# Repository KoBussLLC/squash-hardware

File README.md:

# Squash Keyboard Hardware

Small keyboard for big brains with lots of layers
🤏 ⌨️ 🧠 🍰

This keyboard uses an acrylic case, POM switch-plate, and PCB mounted switches and stabilizers.

See Squash's bigger brother for [build instructions](https://github.com/KoBussLLC/grabert-hardware/blob/main/doc/BUILDGUIDE.md) and [additional information](https://github.com/KoBussLLC/grabert-hardware/blob/main/README.md).

## Layout

[Keyboard Layout Editor Permalink](http://www.keyboard-layout-editor.com/##@@_x:2.75&w:1.5%3B&=0,0&=0,1&=0,2&=0,3&=0,4&=0,5&=0,6&=0,7&=0,8&=0,9&=0,10&_w:1.5%3B&=0,11%3B&@_x:2.75&w:1.75%3B&=1,0&=1,1&=1,2&=1,3&=1,4&=1,5&=1,6&=1,7&=1,8&=1,9&_w:2.25%3B&=1,10%3B&@_x:0.25&w:1.25%3B&=2,0%0A%0A%0A0,1&=2,1%0A%0A%0A0,1&_x:0.25&w:2.25%3B&=2,0%0A%0A%0A0,0&=2,2&=2,3&=2,4&=2,5&=2,6&=2,7&=2,8&=2,9&=2,10&_w:1.75%3B&=2,11%3B&@_x:2.75&c=%23AAAAAA&w:1.25%3B&=3,0&=3,1&=3,2%0A%0A%0A1,0&_c=%23cccccc&w:6.25%3B&=3,4%0A%0A%0A1,0&_c=%23AAAAAA&w:1.25%3B&=3,6&=3,7&_w:1.25%3B&=3,8%3B&@_y:0.25&x:5&w:1.25%3B&=3,2%0A%0A%0A1,1&_c=%23cccccc&w:2.25%3B&=3,3%0A%0A%0A1,1&=3,4%0A%0A%0A1,1&_w:2.75%3B&=3,5%0A%0A%0A1,1&_x:4%3B&=3,11) for layout options.

A standard keycap set can be used as long as each "row" has the same profile and a 1.75u right shift key is included.

## PCB

This project uses KiCad for electrical CAD

### Electrical Design Constraings
- No diode matrix enabled by LQFP 100 Footprint
- STM32 Based Micro-controller
- USB-C
- PWM LED indicators for Caps Lock and modifiers
- PCB Mount switches
- Enocder and I2C OLED Display

## CAD

This project uses FreeCAD 0.19 for mechanical CAD. File names are prefixed with a unique, arbitrary alphanumeric code with the first character always being a alpha character.

### Required Addons
- Assembly 4
- fasteners
- kicadStepUpMod

### Mechanical Design Constraints
- 40% Keyboard Layout
- Split spacebar and left shift layout options
- Push Button Encoder
- OLED Screen
- Fully Laser Cut Case

### Acrylic Sheet Stackup

Main Case Stackup. 0 is the bottom of the case. Foot pieces are included in the D65_USBCutoutSpacer.svg file and are assembled with the smallest piece on the bottom.

| Sheet Number | FreeCAD File Name | Thickness | Material | Shape |
| - | - | - | - | - |
| 0 | O56_BottomPlate | 0.125 in | Acrylic |  |
| 1 | Y7X_ClosedSpacer | 0.125 in | Acrylic |  |
| 2 | D65_USBCutoutSpacer | 0.125 in | Acrylic |  *includes foot pieces |
| 3 | D65_USBCutoutSpacer | 0.125 in | Acrylic |  *includes foot pieces |
| 4 | S86_SwitchPlate | 0.0625 in | POM/Acetal |  |
| 5 | Y7X_ClosedSpacer | 0.125 in | Acrylic |  |
| 6 | Q45_OLEDCover | 0.125 in | Acrylic |  |
| 7 | O03_TopCover | 0.125 in | Acrylic |  |

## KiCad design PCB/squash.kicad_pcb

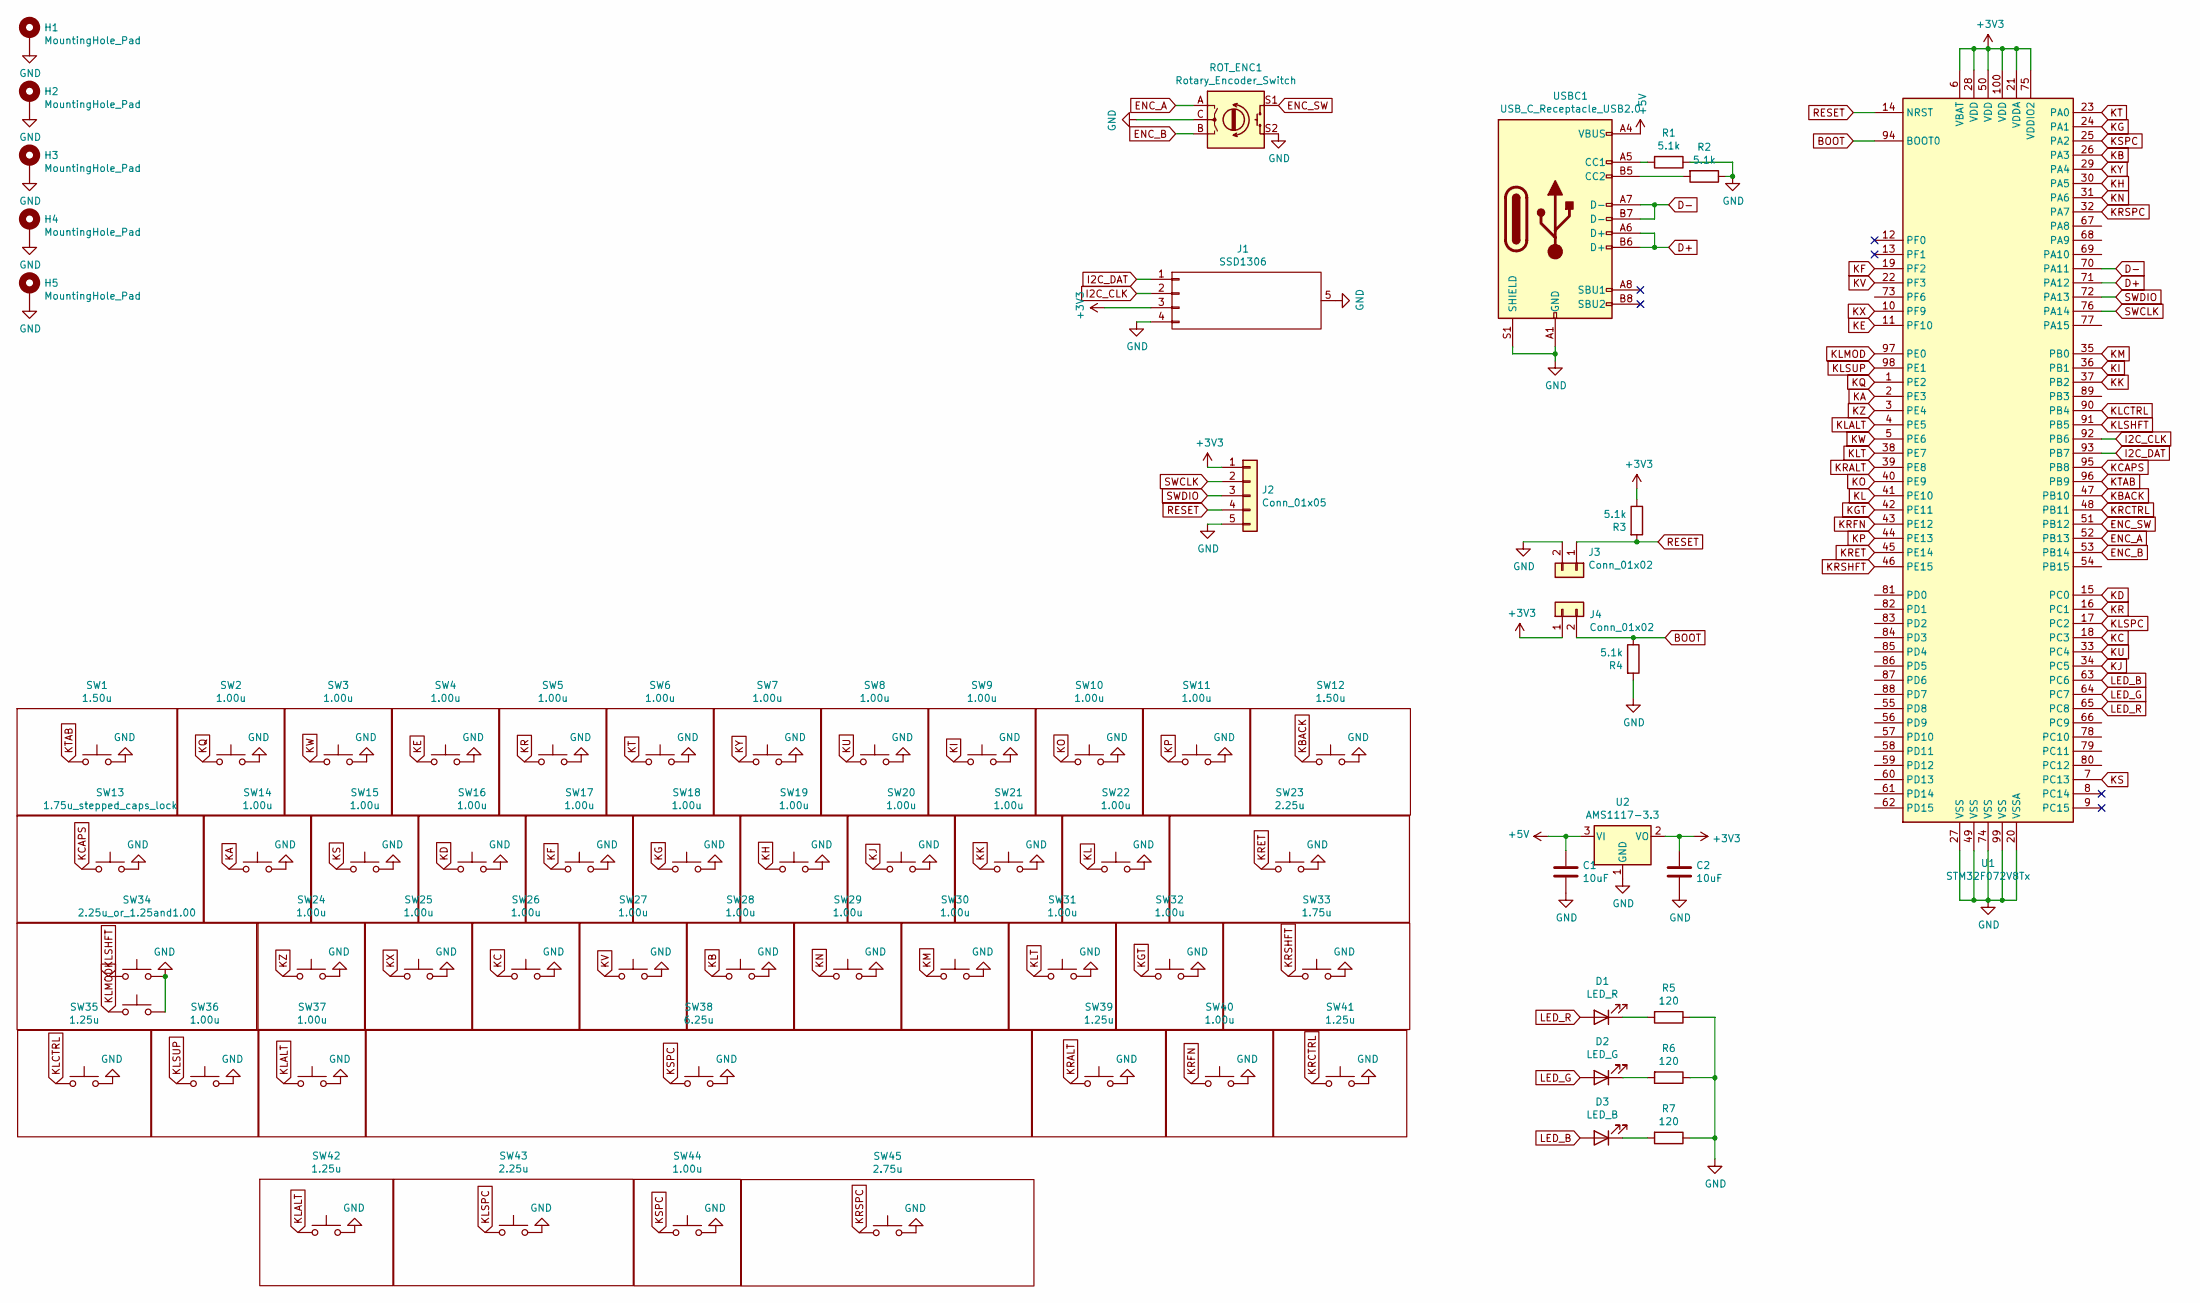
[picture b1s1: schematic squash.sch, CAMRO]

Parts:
C1, C2: 10uF; C_0603_1608Metric
D1: LED_R; LED_0603_1608Metric
D2: LED_G; LED_0603_1608Metric
D3: LED_B; LED_0603_1608Metric
H1, H2, H3, H4, H5: MountingHole_Pad; MountingHole_2.2mm_M2_Pad_Via
J1: SSD1306
J2: Conn_01x05; PinHeader_1x05_P2.54mm_Vertical
J3, J4: Conn_01x02; PinHeader_1x02_P2.54mm_Vertical
R1, R2, R3, R4: 5.1k; R_0603_1608Metric
R5, R6, R7: 120; R_0603_1608Metric
ROT_ENC1: Rotary_Encoder_Switch; RotaryEncoder_Alps_EC11E-Switch_Vertical_H20mm
SW1, SW12: 1.50u; MX_1.50u
SW2, SW3, SW4, SW5, SW6, SW7, SW8, SW9, SW10, SW11, SW14, SW15, SW16, SW17, SW18, SW19, SW20, SW21, SW22, SW24, SW25, SW26, SW27, SW28, SW29, SW30, SW31, SW32, SW36, SW37, SW40, SW44: 1.00u; MX_1u
SW13: 1.75u_stepped_caps_lock; MX_1.75u_stepped_caps
SW23, SW43: 2.25u; MX_2.25u
SW33: 1.75u; MX_1.75u
SW34: 2.25u_or_1.25and1.00; MX_2.25u_or_1.25and1.00
SW35, SW39, SW41, SW42: 1.25u; MX_1.25
SW38: 6.25u; MX_6.25u
SW45: 2.75u; MX_2.75u
U1: STM32F072V8Tx; LQFP-100_14x14mm_P0.5mm
U2: AMS1117-3.3; SOT-223-3_TabPin2
USBC1: USB_C_Receptacle_USB2.0; U262-161N-4BVC11

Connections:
+3V3: C2.1, J1.3 (VCC), J2.1, J4.1, R3.1, U1.6 (VBAT), U1.21 (VDDA), U1.28 (VDD), U1.50 (VDD), U1.75 (VDDIO2), U1.100 (VDD), U2.2 (VO)
+5V: C1.1, U2.3 (VI), USBC1.A4 (VBUS), USBC1.A9 (VBUS), USBC1.B4 (VBUS), USBC1.B9 (VBUS)
BOOT: J4.2, R4.1, U1.94 (BOOT0)
D+: U1.71 (PA12), USBC1.A6 (D+), USBC1.B6 (D+)
D-: U1.70 (PA11), USBC1.A7 (D-), USBC1.B7 (D-)
ENC_A: ROT_ENC1.A, U1.52 (PB13)
ENC_B: ROT_ENC1.B, U1.53 (PB14)
ENC_SW: ROT_ENC1.S1, U1.51 (PB12)
GND: C1.2, C2.2, H1.1, H2.1, H3.1, H4.1, H5.1, J1.4 (GND), J1.5 (MNT), J2.5, J3.2, R1.1, R2.1, R4.2, R5.1, R6.1, R7.1, ROT_ENC1.C, ROT_ENC1.S2, SW1.2, SW2.2, SW3.2, SW4.2, SW5.2, SW6.2, SW7.2, SW8.2, SW9.2, SW10.2, SW11.2, SW12.2, SW13.2, SW14.2, SW15.2, SW16.2, SW17.2, SW18.2, SW19.2, SW20.2, SW21.2, SW22.2, SW23.2, SW24.2, SW25.2, SW26.2, SW27.2, SW28.2, SW29.2, SW30.2, SW31.2, SW32.2, SW33.2, SW34.2, SW35.2, SW36.2, SW37.2, SW38.2, SW39.2, SW40.2, SW41.2, SW42.2, SW43.2, SW44.2, SW45.2, U1.20 (VSSA), U1.27 (VSS), U1.49 (VSS), U1.74 (VSS), U1.99 (VSS), U2.1 (GND), USBC1.A1 (GND), USBC1.A12 (GND), USBC1.B1 (GND), USBC1.B12 (GND), USBC1.S1 (SHIELD)
I2C_CLK: J1.2 (SCL), U1.92 (PB6)
I2C_DAT: J1.1 (SDA), U1.93 (PB7)
KA: SW14.1, U1.2 (PE3)
KB: SW28.1, U1.26 (PA3)
KBACK: SW12.1, U1.47 (PB10)
KC: SW26.1, U1.18 (PC3)
KCAPS: SW13.1, U1.95 (PB8)
KD: SW16.1, U1.15 (PC0)
KE: SW4.1, U1.11 (PF10)
KF: SW17.1, U1.19 (PF2)
KG: SW18.1, U1.24 (PA1)
KGT: SW32.1, U1.42 (PE11)
KH: SW19.1, U1.30 (PA5)
KI: SW9.1, U1.36 (PB1)
KJ: SW20.1, U1.34 (PC5)
KK: SW21.1, U1.37 (PB2)
KL: SW22.1, U1.41 (PE10)
KLALT: SW37.1, SW42.1, U1.4 (PE5)
KLCTRL: SW35.1, U1.90 (PB4)
KLMOD: SW34.3, U1.97 (PE0)
KLSHFT: SW34.1, U1.91 (PB5)
KLSPC: SW43.1, U1.17 (PC2)
KLSUP: SW36.1, U1.98 (PE1)
KLT: SW31.1, U1.38 (PE7)
KM: SW30.1, U1.35 (PB0)
KN: SW29.1, U1.31 (PA6)
KO: SW10.1, U1.40 (PE9)
KP: SW11.1, U1.44 (PE13)
KQ: SW2.1, U1.1 (PE2)
KR: SW5.1, U1.16 (PC1)
KRALT: SW39.1, U1.39 (PE8)
KRCTRL: SW41.1, U1.48 (PB11)
KRET: SW23.1, U1.45 (PE14)
KRFN: SW40.1, U1.43 (PE12)
KRSHFT: SW33.1, U1.46 (PE15)
KRSPC: SW45.1, U1.32 (PA7)
KS: SW15.1, U1.7 (PC13)
KSPC: SW38.1, SW44.1, U1.25 (PA2)
KT: SW6.1, U1.23 (PA0)
KTAB: SW1.1, U1.96 (PB9)
KU: SW8.1, U1.33 (PC4)
KV: SW27.1, U1.22 (PF3)
KW: SW3.1, U1.5 (PE6)
KX: SW25.1, U1.10 (PF9)
KY: SW7.1, U1.29 (PA4)
KZ: SW24.1, U1.3 (PE4)
LED_B: D3.2 (A), U1.63 (PC6)
LED_G: D2.2 (A), U1.64 (PC7)
LED_R: D1.2 (A), U1.65 (PC8)
unnamed: D1.1 (K), R5.2
unnamed: D2.1 (K), R6.2
unnamed: D3.1 (K), R7.2
unnamed: R1.2, USBC1.A5 (CC1)
unnamed: R2.2, USBC1.B5 (CC2)
RESET: J2.4, J3.1, R3.2, U1.14 (NRST)
SWCLK: J2.2, U1.76 (PA14)
SWDIO: J2.3, U1.72 (PA13)

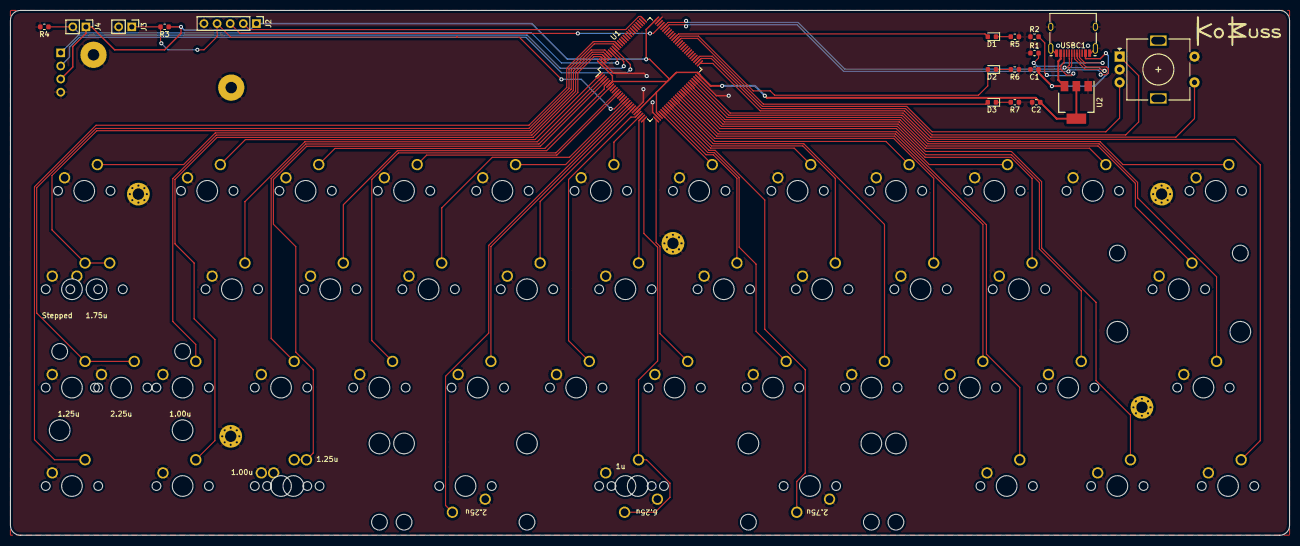
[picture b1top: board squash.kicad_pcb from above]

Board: 2 copper layers, 247.7 x 101.6 mm, 73 parts (1 on the bottom side), 66 nets.

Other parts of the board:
Ref**: Val**; Squash2
Ref**#2, Ref**#3: Val**; kobuss_name

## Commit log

2020-10-24 V0 Squash PCB
2020-10-24 Initial switch plate CAD
2020-10-24 Case Clear Top Cover
2020-10-25 Case Foundation CAD
2020-11-13 Closed case with foot
2020-11-13 Left alt key pcb label, removal of logo
2020-12-09 Bottom foot hole dia down to 2.2mm
2021-01-06 Updated vector cut files
2021-01-06 assem update
2021-01-07 general information added
2021-01-31 main squash image
2021-05-14 V0 case finalize
